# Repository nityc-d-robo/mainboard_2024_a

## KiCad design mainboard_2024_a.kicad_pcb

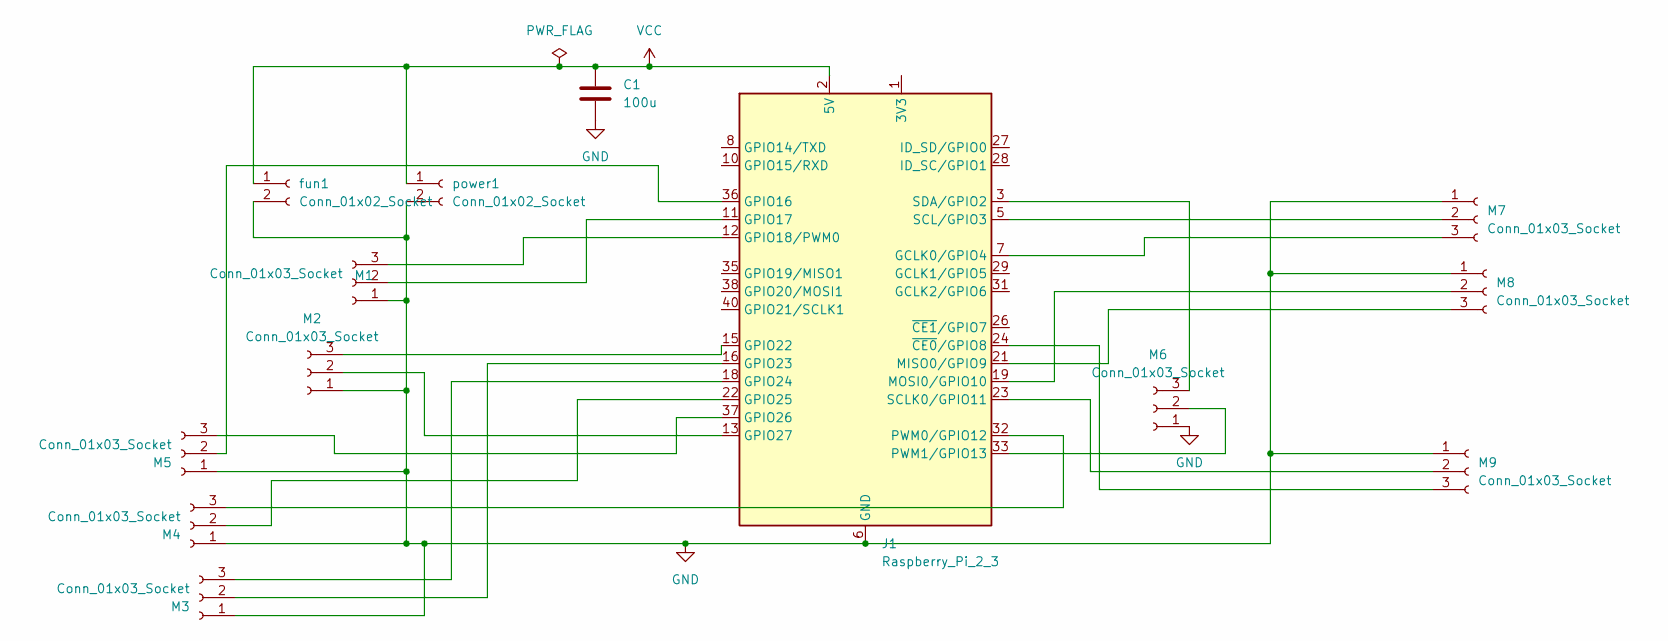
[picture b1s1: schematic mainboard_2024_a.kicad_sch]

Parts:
C1: 100u; C_1206_3216Metric_Pad1.33x1.80mm_HandSolder
J1: Raspberry_Pi_2_3; Raspberry_Pi_Zero_Socketed_THT_FaceDown_MountingHoles
M1, M2, M3, M4, M5, M6, M7, M8, M9: Conn_01x03_Socket; JST_XH_B3B-XH-A_1x03_P2.50mm_Vertical
fun1: Conn_01x02_Socket; JST_XH_B2B-XH-A_1x02_P2.50mm_Vertical
power1: Conn_01x02_Socket; JST_XH_B2B-XH-A_1x02_P2.50mm_Vertical

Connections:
GND: C1.2, J1.6 (GND), J1.9 (GND), J1.14 (GND), J1.20 (GND), J1.25 (GND), J1.30 (GND), J1.34 (GND), J1.39 (GND), M1.1, M2.1, M3.1, M4.1, M5.1, M6.1, M7.1, M8.1, M9.1, fun1.2, power1.2
unnamed: J1.1 (3V3), J1.17 (3V3)
unnamed: J1.7 (GCLK0/GPIO4), M7.3
unnamed: J1.36 (GPIO16), M5.2
unnamed: J1.11 (GPIO17), M1.2
unnamed: J1.12 (GPIO18/PWM0), M1.3
unnamed: J1.15 (GPIO22), M2.3
unnamed: J1.16 (GPIO23), M3.2
unnamed: J1.18 (GPIO24), M3.3
unnamed: J1.22 (GPIO25), M4.2
unnamed: J1.37 (GPIO26), M5.3
unnamed: J1.13 (GPIO27), M2.2
unnamed: J1.21 (MISO0/GPIO9), M8.3
unnamed: J1.19 (MOSI0/GPIO10), M8.2
unnamed: J1.32 (PWM0/GPIO12), M4.3
unnamed: J1.33 (PWM1/GPIO13), M6.2
unnamed: J1.23 (SCLK0/GPIO11), M9.2
unnamed: J1.5 (SCL/GPIO3), M7.2
unnamed: J1.3 (SDA/GPIO2), M6.3
unnamed: J1.24 (~CE0/GPIO8), M9.3
VCC: C1.1, J1.2 (5V), J1.4 (5V), fun1.1, power1.1

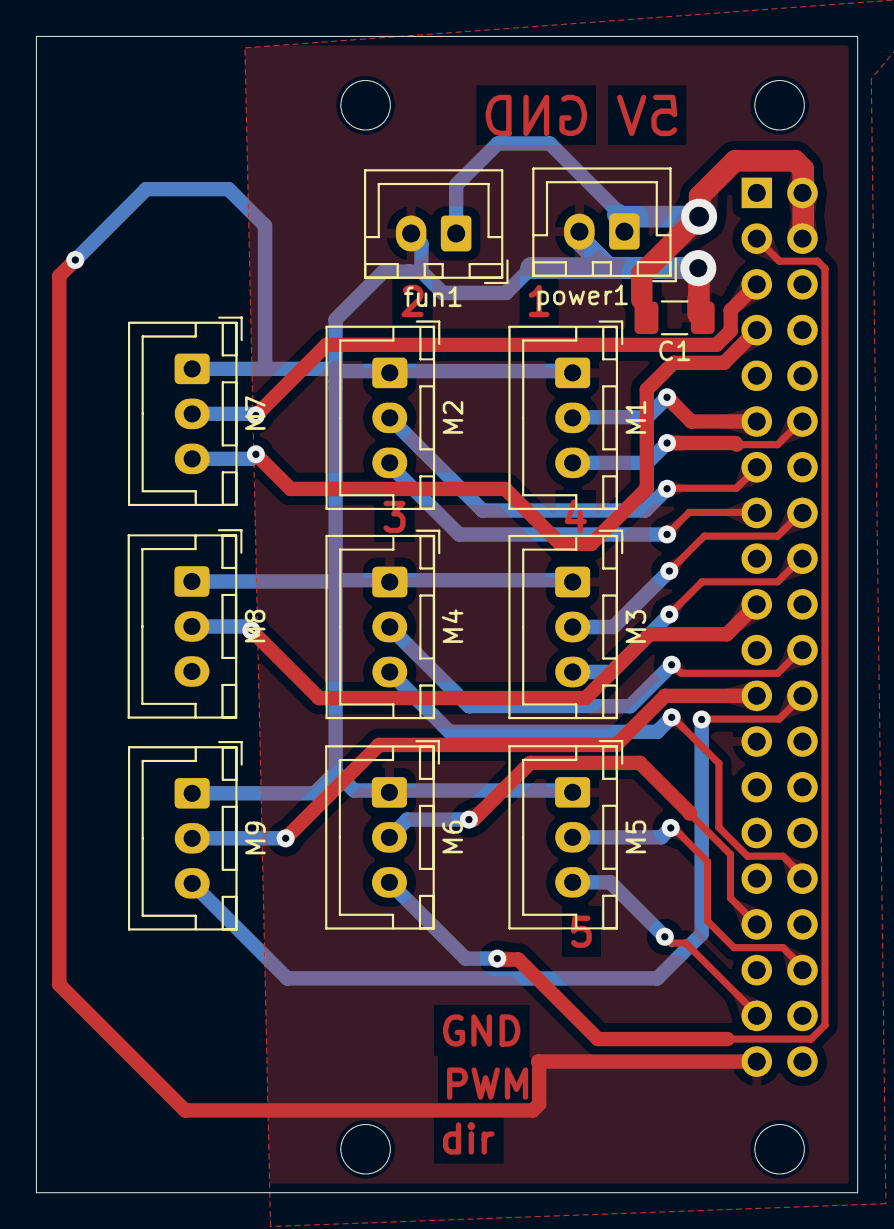
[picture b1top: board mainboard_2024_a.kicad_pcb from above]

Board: 2 copper layers, 45.6 x 64.2 mm, 13 parts (1 on the bottom side), 21 nets.

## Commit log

2024-07-12 add text
2024-07-13 ロボコン辞めます
2024-09-11 add 7 8 9
